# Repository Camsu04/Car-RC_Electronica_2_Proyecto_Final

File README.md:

# Car RC_Electronica_2_Proyecto_Final
Carrito a Control Remoto con 5 Aplicaciones y controlado mediantre esp32

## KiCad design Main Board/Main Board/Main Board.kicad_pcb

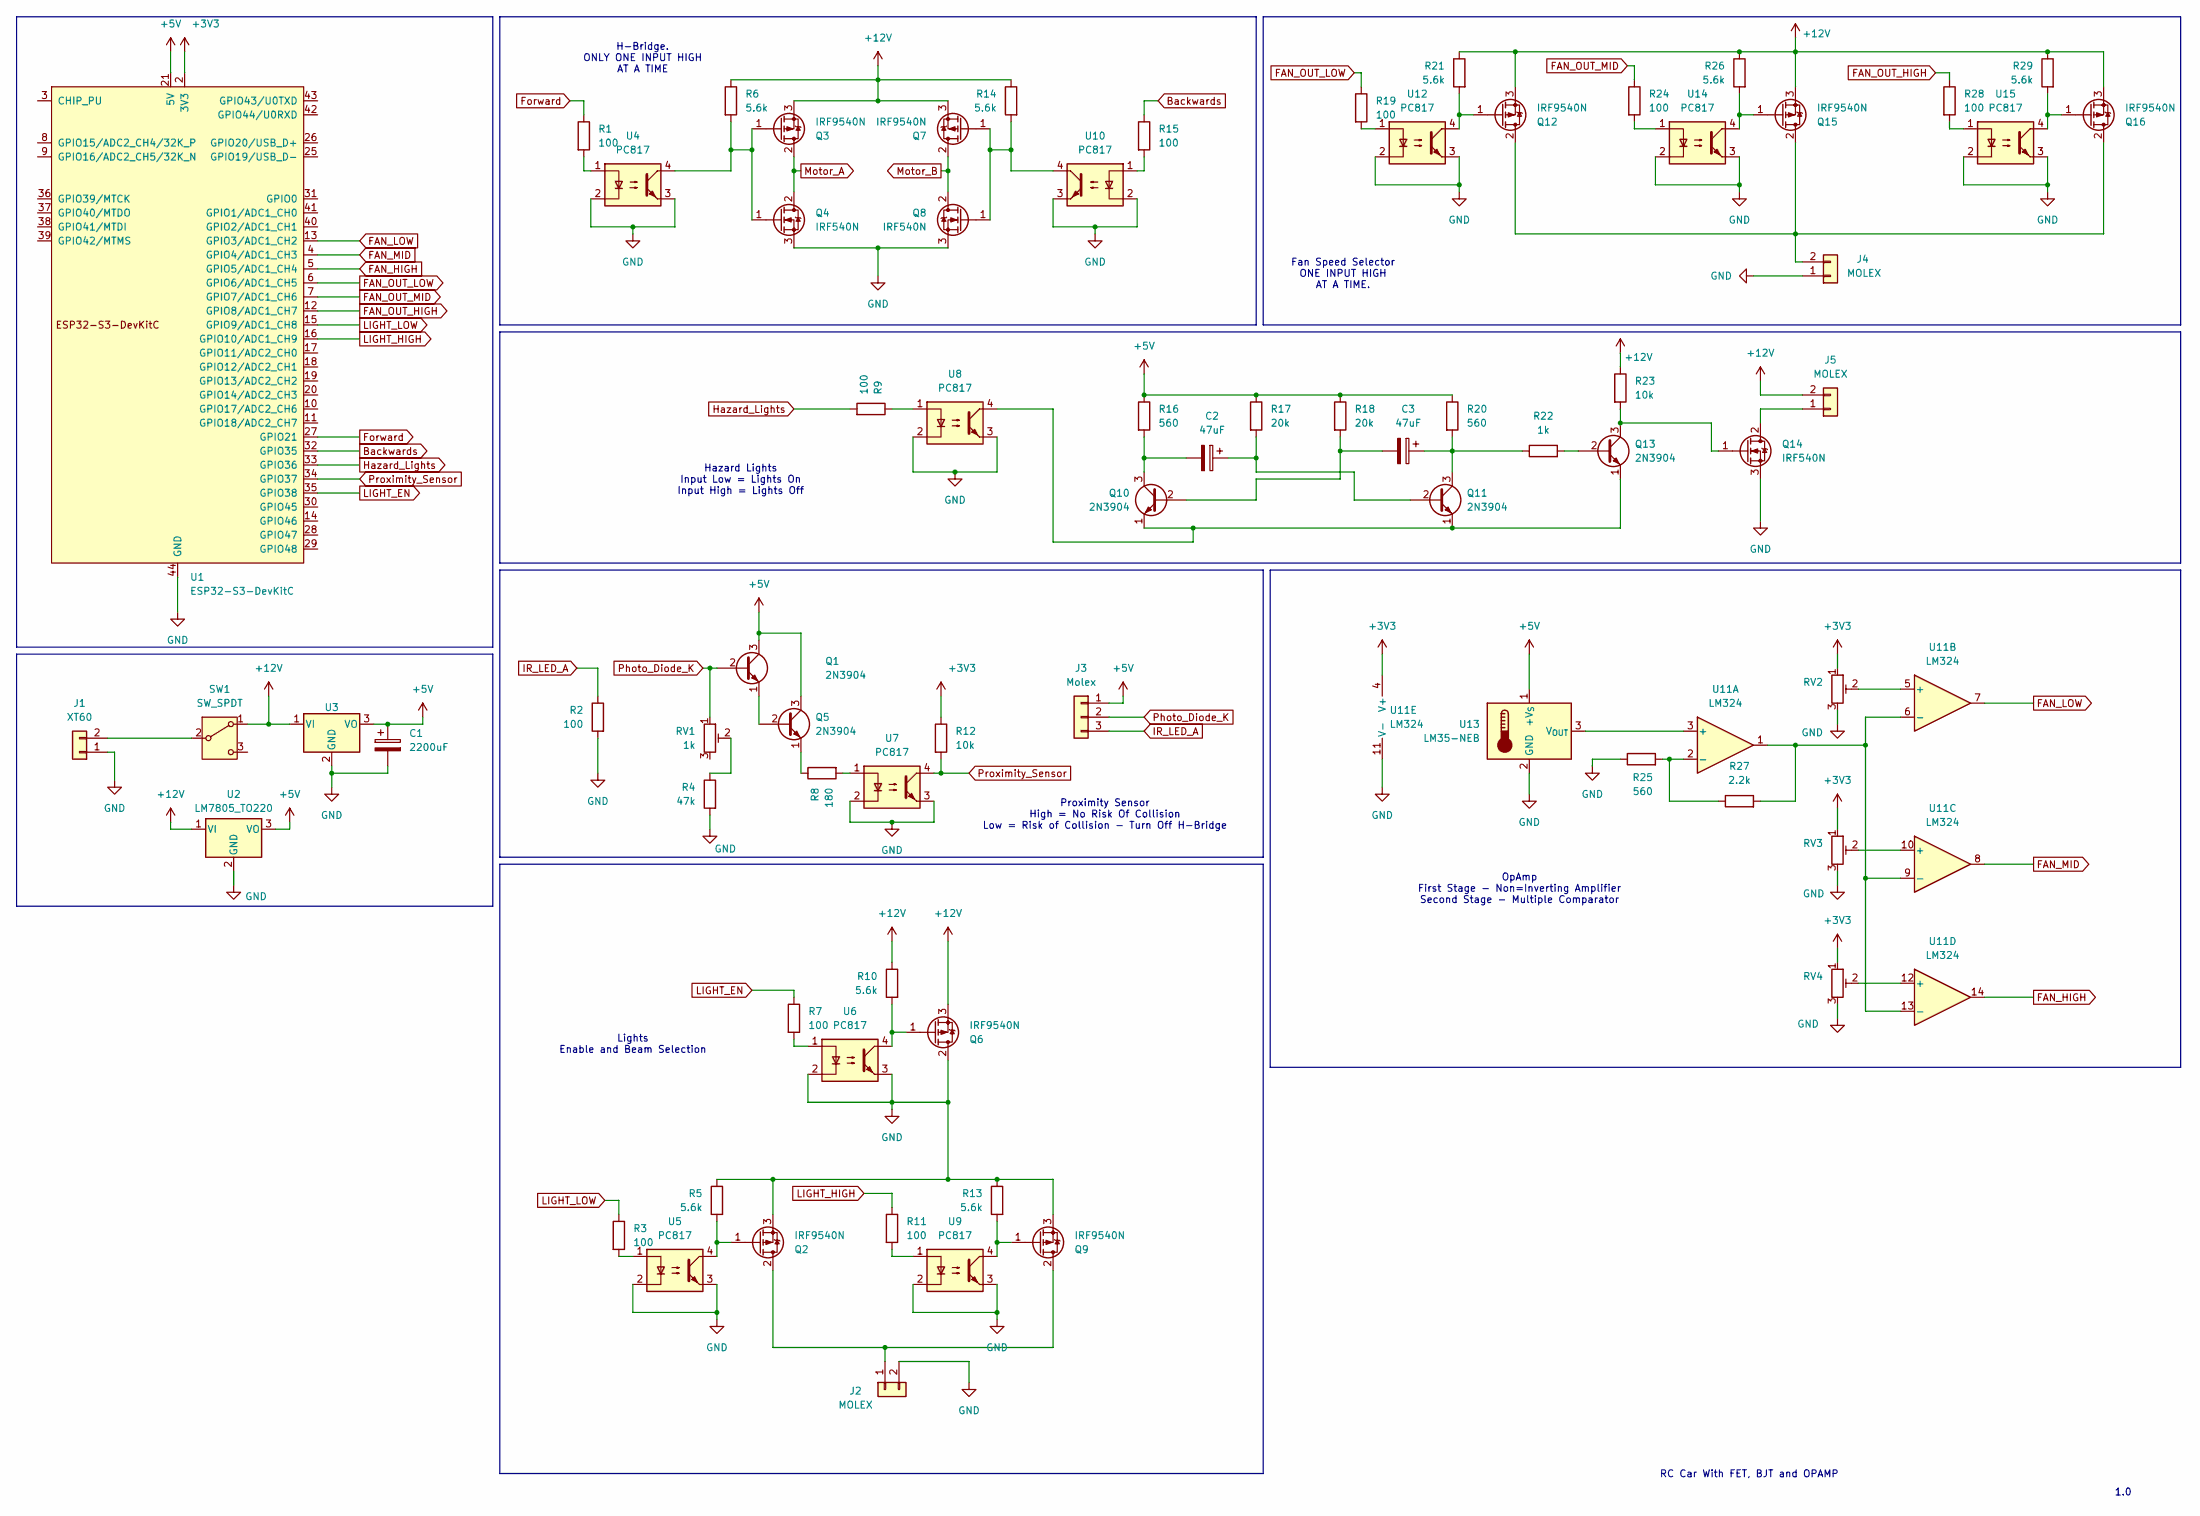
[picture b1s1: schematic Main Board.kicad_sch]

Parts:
C1: 2200uF; CP_Radial_D12.5mm_P5.00mm
C2, C3: 47uF; CP_Radial_D5.0mm_P2.50mm
J1: XT60; AMASS_XT60-M_1x02_P7.20mm_Vertical
J2, J4, J5: MOLEX; Molex_KK-254_AE-6410-02A_1x02_P2.54mm_Vertical
J3: Molex; Molex_KK-254_AE-6410-03A_1x03_P2.54mm_Vertical
Q1, Q5, Q10, Q11, Q13: 2N3904; TO-92_Inline
Q2, Q3, Q6, Q7, Q9, Q12, Q15, Q16: IRF9540N; TO-220-3_Vertical
Q4, Q8, Q14: IRF540N; TO-220-3_Vertical
R1, R2, R3, R7, R9, R11, R15, R19, R24, R28: 100; R_Axial_DIN0309_L9.0mm_D3.2mm_P15.24mm_Horizontal
R4: 47k; R_Axial_DIN0309_L9.0mm_D3.2mm_P15.24mm_Horizontal
R5, R6, R10, R13, R14, R21, R26, R29: 5.6k; R_Axial_DIN0309_L9.0mm_D3.2mm_P15.24mm_Horizontal
R8: 180; R_Axial_DIN0309_L9.0mm_D3.2mm_P15.24mm_Horizontal
R12, R23: 10k; R_Axial_DIN0309_L9.0mm_D3.2mm_P15.24mm_Horizontal
R16, R20, R25: 560; R_Axial_DIN0309_L9.0mm_D3.2mm_P15.24mm_Horizontal
R17, R18: 20k; R_Axial_DIN0309_L9.0mm_D3.2mm_P15.24mm_Horizontal
R22: 1k; R_Axial_DIN0309_L9.0mm_D3.2mm_P15.24mm_Horizontal
R27: 2.2k; R_Axial_DIN0309_L9.0mm_D3.2mm_P15.24mm_Horizontal
RV1: 1k; Potentiometer_Runtron_RM-065_Vertical
RV2, RV3, RV4: R_Potentiometer_Trim; Potentiometer_Runtron_RM-065_Vertical
SW1: SW_SPDT; SW_Toggle_Blue_wSlots
U1: ESP32-S3-DevKitC
U2, U3: LM7805_TO220; TO-220-3_Vertical
U4, U5, U6, U7, U8, U9, U10, U12, U14, U15: PC817; DIP-4_W7.62mm
U11: LM324; DIP-14_W7.62mm_LongPads
U13: LM35-NEB; TO-220-3_Vertical

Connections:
+3V3: R12.1, RV2.1, RV3.1, RV4.1, U1.1 (3V3), U1.2 (3V3), U11.4 (V+)
+5V: C1.1, J3.1, Q1.3 (C), Q5.3 (C), R16.1, R17.1, R18.1, R20.1, U1.21 (5V), U2.3 (VO), U3.3 (VO), U13.1 (+V_{S})
+12V: J5.2, Q3.3 (S), Q6.3 (S), Q7.3 (S), Q12.3 (S), Q15.3 (S), Q16.3 (S), R6.1, R10.1, R14.1, R21.1, R23.1, R26.1, R29.1, SW1.1 (A), U2.1 (VI), U3.1 (VI)
Backwards: R15.1, U1.32 (GPIO35)
FAN_HIGH: U1.5 (GPIO5/ADC1_CH4), U11.14
FAN_LOW: U1.13 (GPIO3/ADC1_CH2), U11.7
FAN_MID: U1.4 (GPIO4/ADC1_CH3), U11.8
FAN_OUT_HIGH: R28.1, U1.12 (GPIO8/ADC1_CH7)
FAN_OUT_LOW: R19.1, U1.6 (GPIO6/ADC1_CH5)
FAN_OUT_MID: R24.1, U1.7 (GPIO7/ADC1_CH6)
Forward: R1.1, U1.27 (GPIO21)
GND: C1.2, J1.1, J2.2, J4.1, Q2.3 (S), Q4.3 (S), Q6.2 (D), Q8.3 (S), Q9.3 (S), Q14.3 (S), R2.2, R4.2, R5.1, R13.1, R25.1, RV2.3, RV3.3, RV4.3, U1.22 (GND), U1.23 (GND), U1.24 (GND), U1.44 (GND), U2.2 (GND), U3.2 (GND), U4.2, U4.3, U5.2, U5.3, U6.2, U6.3, U7.2, U7.3, U8.2, U8.3, U9.2, U9.3, U10.2, U10.3, U11.11 (V-), U12.2, U12.3, U13.2 (GND), U14.2, U14.3, U15.2, U15.3
Hazard_Lights: R9.2, U1.33 (GPIO36)
IR_LED_A: J3.3, R2.1
LIGHT_EN: R7.1, U1.35 (GPIO38)
LIGHT_HIGH: R11.1, U1.16 (GPIO10/ADC1_CH9)
LIGHT_LOW: R3.1, U1.15 (GPIO9/ADC1_CH8)
Motor_A: Q3.2 (D), Q4.2 (D); also elsewhere on the board
Motor_B: Q7.2 (D), Q8.2 (D); also elsewhere on the board
unnamed: J1.2, SW1.2 (B)
unnamed: J2.1, Q2.2 (D), Q9.2 (D)
unnamed: J4.2, Q12.2 (D), Q15.2 (D), Q16.2 (D)
unnamed: J5.1, Q14.2 (D)
unnamed: Q1.1 (E), Q5.2 (B)
unnamed: Q2.1 (G), R5.2, U5.4
unnamed: Q3.1 (G), Q4.1 (G), R6.2, U4.4
unnamed: Q5.1 (E), R8.1
unnamed: Q6.1 (G), R10.2, U6.4
unnamed: Q7.1 (G), Q8.1 (G), R14.2, U10.4
unnamed: Q9.1 (G), R13.2, U9.4
unnamed: C3.2, Q10.2 (B), R18.2
unnamed: C2.2, Q10.3 (C), R16.2
unnamed: Q10.1 (E), Q11.1 (E), Q13.1 (E), U8.4
unnamed: C2.1, Q11.2 (B), R17.2
unnamed: C3.1, Q11.3 (C), R20.2, R22.1
unnamed: Q12.1 (G), R21.2, U12.4
unnamed: Q13.2 (B), R22.2
unnamed: Q13.3 (C), Q14.1 (G), R23.2
unnamed: Q15.1 (G), R26.2, U14.4
unnamed: Q16.1 (G), R29.2, U15.4
unnamed: R1.2, U4.1
unnamed: R3.2, U5.1
unnamed: R4.1, RV1.2
unnamed: R7.2, U6.1
unnamed: R8.2, U7.1
unnamed: R9.1, U8.1
unnamed: R11.2, U9.1
unnamed: R15.2, U10.1
unnamed: R19.2, U12.1
unnamed: R24.2, U14.1
unnamed: R28.2, U15.1
unnamed: U11.3 (+), U13.3 (V_{OUT})
unnamed: R25.2, R27.1, U11.2 (-)
unnamed: RV2.2, U11.5 (+)
unnamed: R27.2, U11.1, U11.6 (-), U11.9 (-), U11.13 (-)
unnamed: RV3.2, U11.10 (+)
unnamed: RV4.2, U11.12 (+)
Photo_Diode_K: J3.2, Q1.2 (B), RV1.1
Proximity_Sensor: R12.2, U1.34 (GPIO37), U7.4

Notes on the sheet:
H-Bridge. ONLY ONE INPUT HIGH AT A TIME
RC Car With FET, BJT and OPAMP
Hazard Lights Input Low = Lights On Input High = Lights Off
1.0
Lights Enable and Beam Selection
Proximity Sensor High = No Risk Of Collision Low = Risk of Collision - Turn Off H-Bridge
Fan Speed Selector ONE INPUT HIGH AT A TIME.
OpAmp First Stage - Non=Inverting Amplifier Second Stage - Multiple Comparator

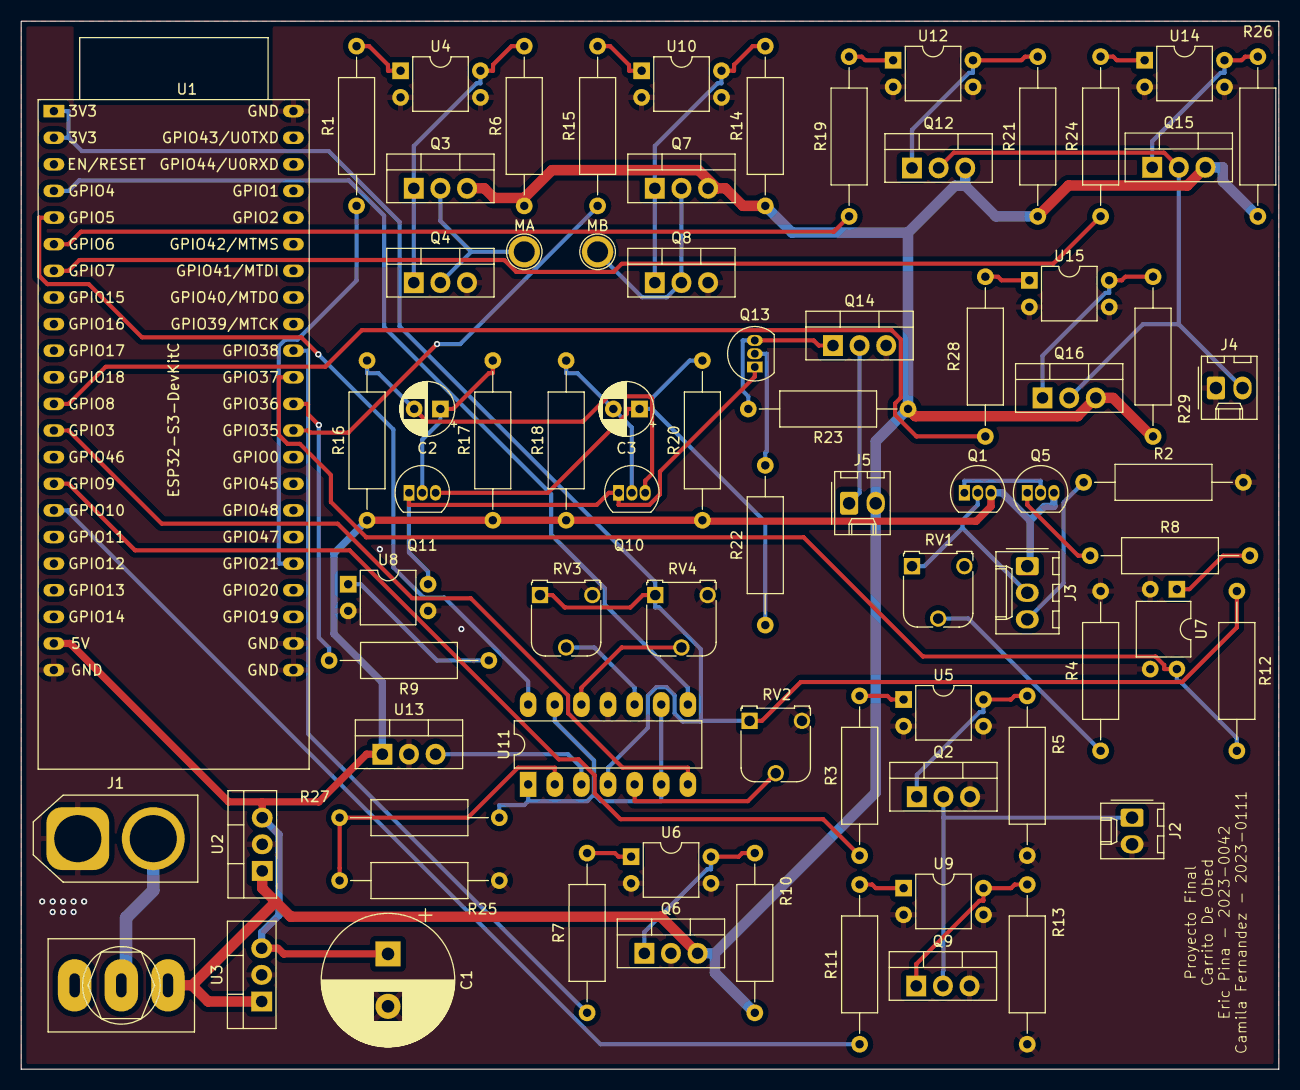
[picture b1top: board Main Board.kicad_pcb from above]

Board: 2 copper layers, 120.0 x 100.0 mm, 75 parts (0 on the bottom side), 59 nets.

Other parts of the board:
MA: TestPoint_Plated_Hole_D2.0mm
MB: TestPoint_Plated_Hole_D2.0mm

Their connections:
Motor_A: MA.1; also elsewhere on the board
Motor_B: MB.1; also elsewhere on the board

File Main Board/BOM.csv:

"Reference","Value","Datasheet","Footprint","Qty","DNP"
"C1","2200uF","~","Capacitor_THT:CP_Radial_D12.5mm_P5.00mm","1",""
"C2,C3","47uF","~","Capacitor_THT:CP_Radial_D5.0mm_P2.50mm","2",""
"J1","XT60","~","Connector_AMASS:AMASS_XT60-M_1x02_P7.20mm_Vertical","1",""
"J2,J4,J5","MOLEX","~","Connector_Molex:Molex_KK-254_AE-6410-02A_1x02_P2.54mm_Vertical","3",""
"J3","Molex","~","Connector_Molex:Molex_KK-254_AE-6410-03A_1x03_P2.54mm_Vertical","1",""
"Q1,Q5,Q10,Q11,Q13","2N3904","https://www.onsemi.com/pub/Collateral/2N3903-D.PDF","Package_TO_SOT_THT:TO-92_Inline","5",""
"Q2,Q3,Q6,Q7,Q9,Q12,Q15,Q16","IRF9540N","http://www.irf.com/product-info/datasheets/data/irf9540n.pdf","Package_TO_SOT_THT:TO-220-3_Vertical","8",""
"Q4,Q8,Q14","IRF540N","http://www.irf.com/product-info/datasheets/data/irf540n.pdf","Package_TO_SOT_THT:TO-220-3_Vertical","3",""
"R1,R2,R3,R7,R9,R11,R15,R19,R24,R28","100","~","Resistor_THT:R_Axial_DIN0309_L9.0mm_D3.2mm_P15.24mm_Horizontal","10",""
"R4","47k","~","Resistor_THT:R_Axial_DIN0309_L9.0mm_D3.2mm_P15.24mm_Horizontal","1",""
"R5,R6,R10,R13,R14,R21,R26,R29","5.6k","~","Resistor_THT:R_Axial_DIN0309_L9.0mm_D3.2mm_P15.24mm_Horizontal","8",""
"R8","180","~","Resistor_THT:R_Axial_DIN0309_L9.0mm_D3.2mm_P15.24mm_Horizontal","1",""
"R12,R23","10k","~","Resistor_THT:R_Axial_DIN0309_L9.0mm_D3.2mm_P15.24mm_Horizontal","2",""
"R16,R20,R25","560","~","Resistor_THT:R_Axial_DIN0309_L9.0mm_D3.2mm_P15.24mm_Horizontal","3",""
"R17,R18","20k","~","Resistor_THT:R_Axial_DIN0309_L9.0mm_D3.2mm_P15.24mm_Horizontal","2",""
"R22,RV1","1k","~","-- mixed values --","2",""
"R27","2.2k","~","Resistor_THT:R_Axial_DIN0309_L9.0mm_D3.2mm_P15.24mm_Horizontal","1",""
"RV2,RV3,RV4","R_Potentiometer_Trim","~","Potentiometer_THT:Potentiometer_Runtron_RM-065_Vertical","3",""
"SW1","SW_SPDT","~","Toggle:SW_Toggle_Blue_wSlots","1",""
"U1","ESP32-S3-DevKitC","","PCM_Espressif:ESP32-S3-DevKitC","1",""
"U2,U3","LM7805_TO220","https://www.onsemi.cn/PowerSolutions/document/MC7800-D.PDF","Package_TO_SOT_THT:TO-220-3_Vertical","2",""
"U4,U5,U6,U7,U8,U9,U10,U12,U14,U15","PC817","http://www.soselectronic.cz/a_info/resource/d/pc817.pdf","Package_DIP:DIP-4_W7.62mm","10",""
"U11","LM324","http://www.ti.com/lit/ds/symlink/lm2902-n.pdf","Package_DIP:DIP-14_W7.62mm_LongPads","1",""
"U13","LM35-NEB","http://www.ti.com/lit/ds/symlink/lm35.pdf","Package_TO_SOT_THT:TO-220-3_Vertical","1",""

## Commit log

2025-07-19 Docs
